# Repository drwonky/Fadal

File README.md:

# Fadal
Fadal reverse engineering schematics

- eagle/ contains some older Eagle schematics
- kicad/ contains imported Eagle schematics and some native schematics

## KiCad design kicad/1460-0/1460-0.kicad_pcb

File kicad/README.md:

## Fadal schematics
---
#### Note
The path to the S100.lbr was changed before committing to this repo to redact path names, you will need to update this yourself if you want to reference the S100 components.
---
- 1030-0e - imported from eagle
- 1090-2 - imported from eagle
- 1400-1A - imported from eagle
- 1420-1 - imported from eagle
- 1460-0 - Schematic and board layout, no routing
- components - custom componentes
- P8212.zip - Online EDA conversion of S100 component
- P8216.zip - Online EDA conversion of S100 component
- P8284.zip - Online EDA conversion of S100 component
- S100_MALE.kicad_mod - Kicad conversion
- S100_MALE.zip - Online EDA conversion of S100 component

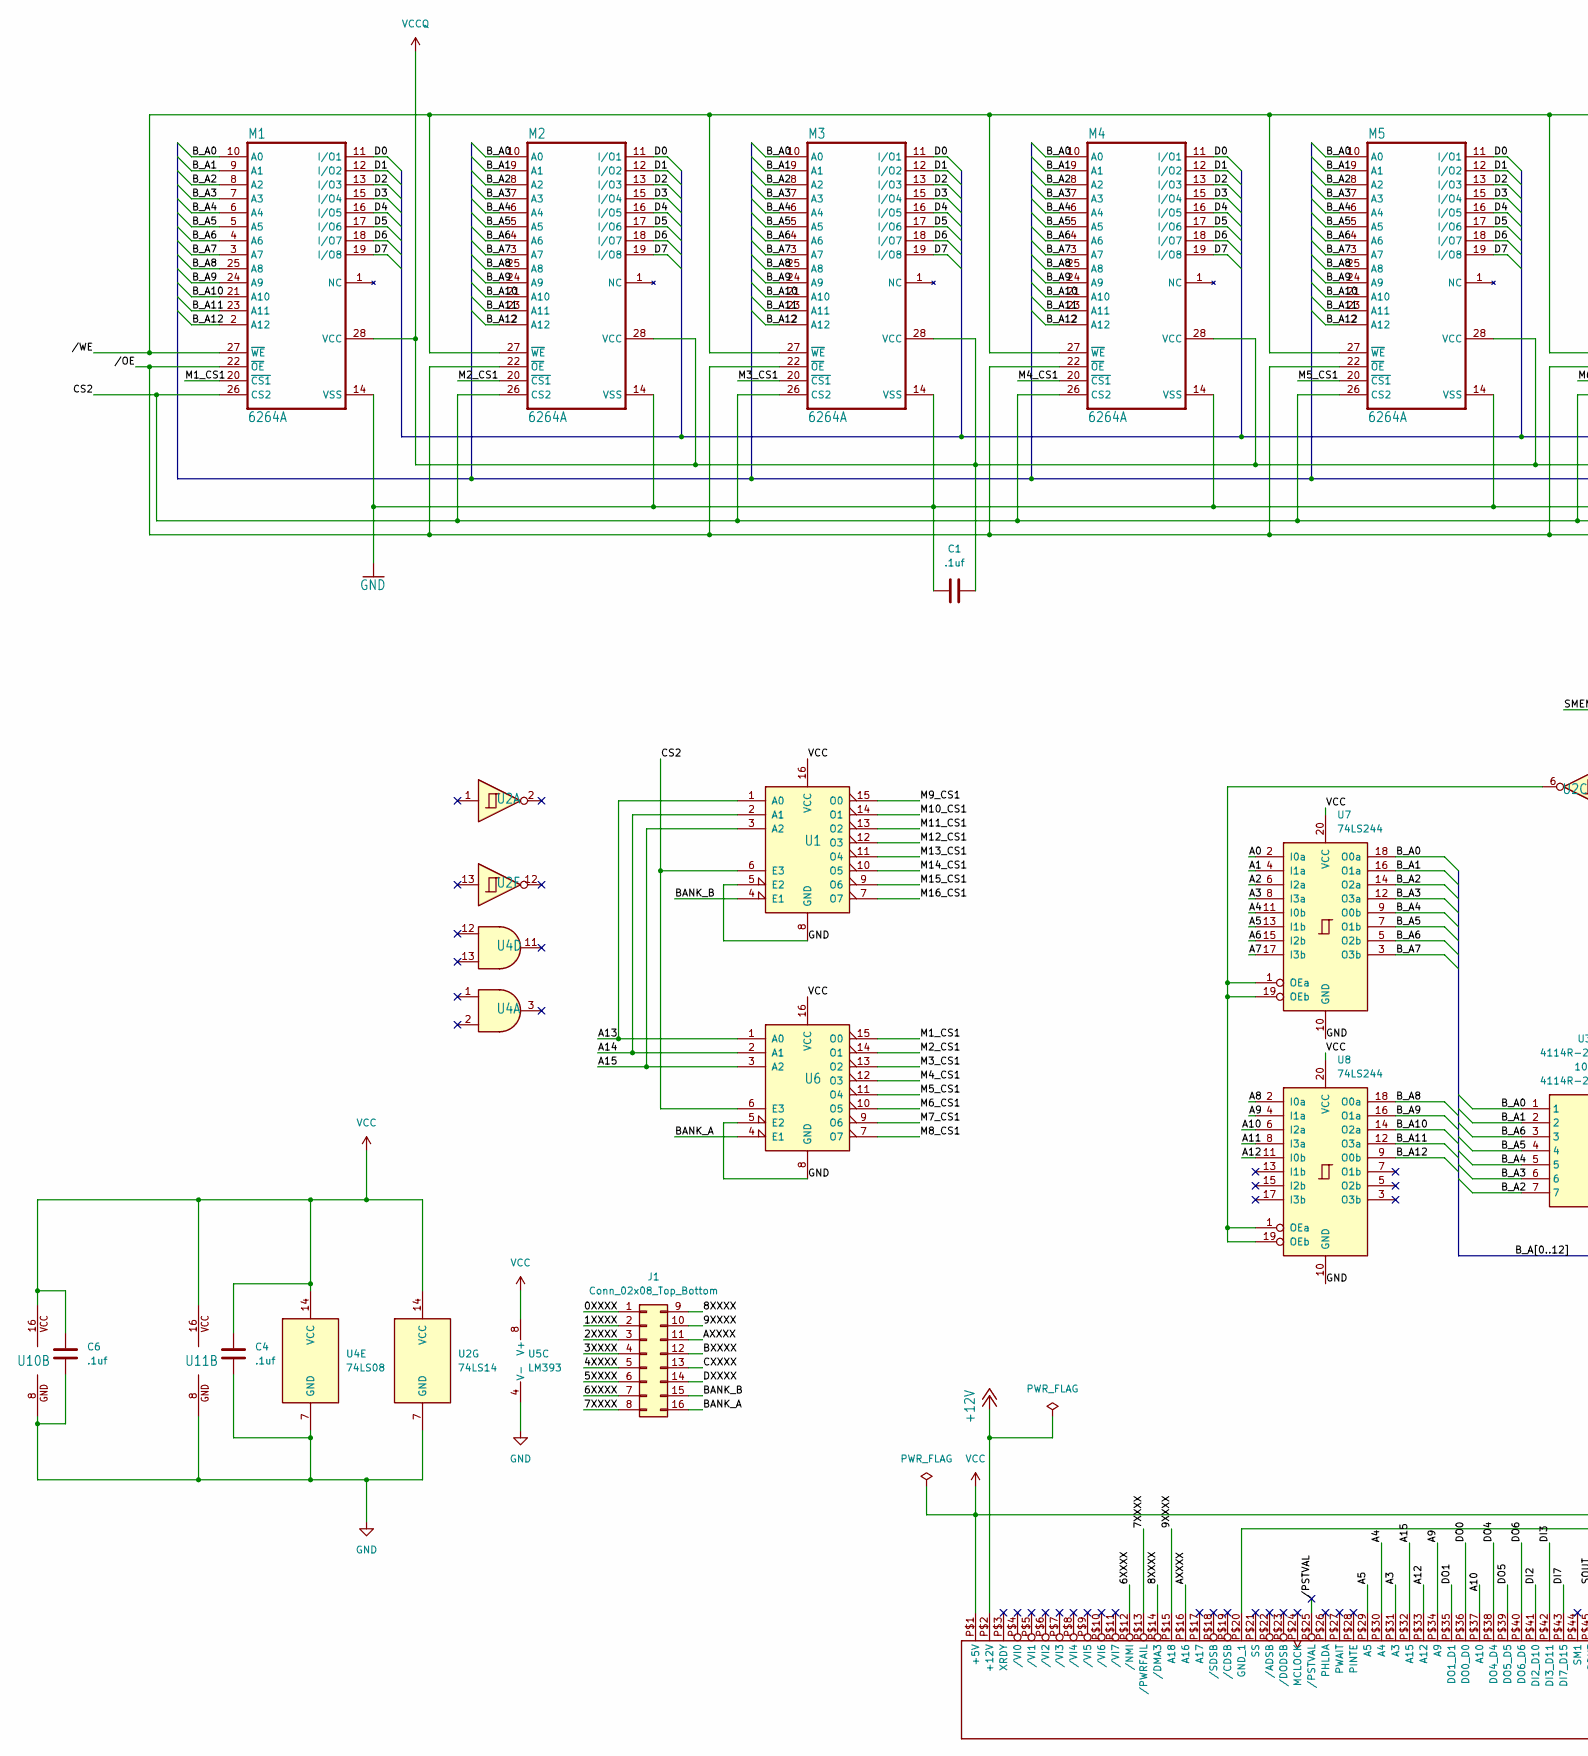
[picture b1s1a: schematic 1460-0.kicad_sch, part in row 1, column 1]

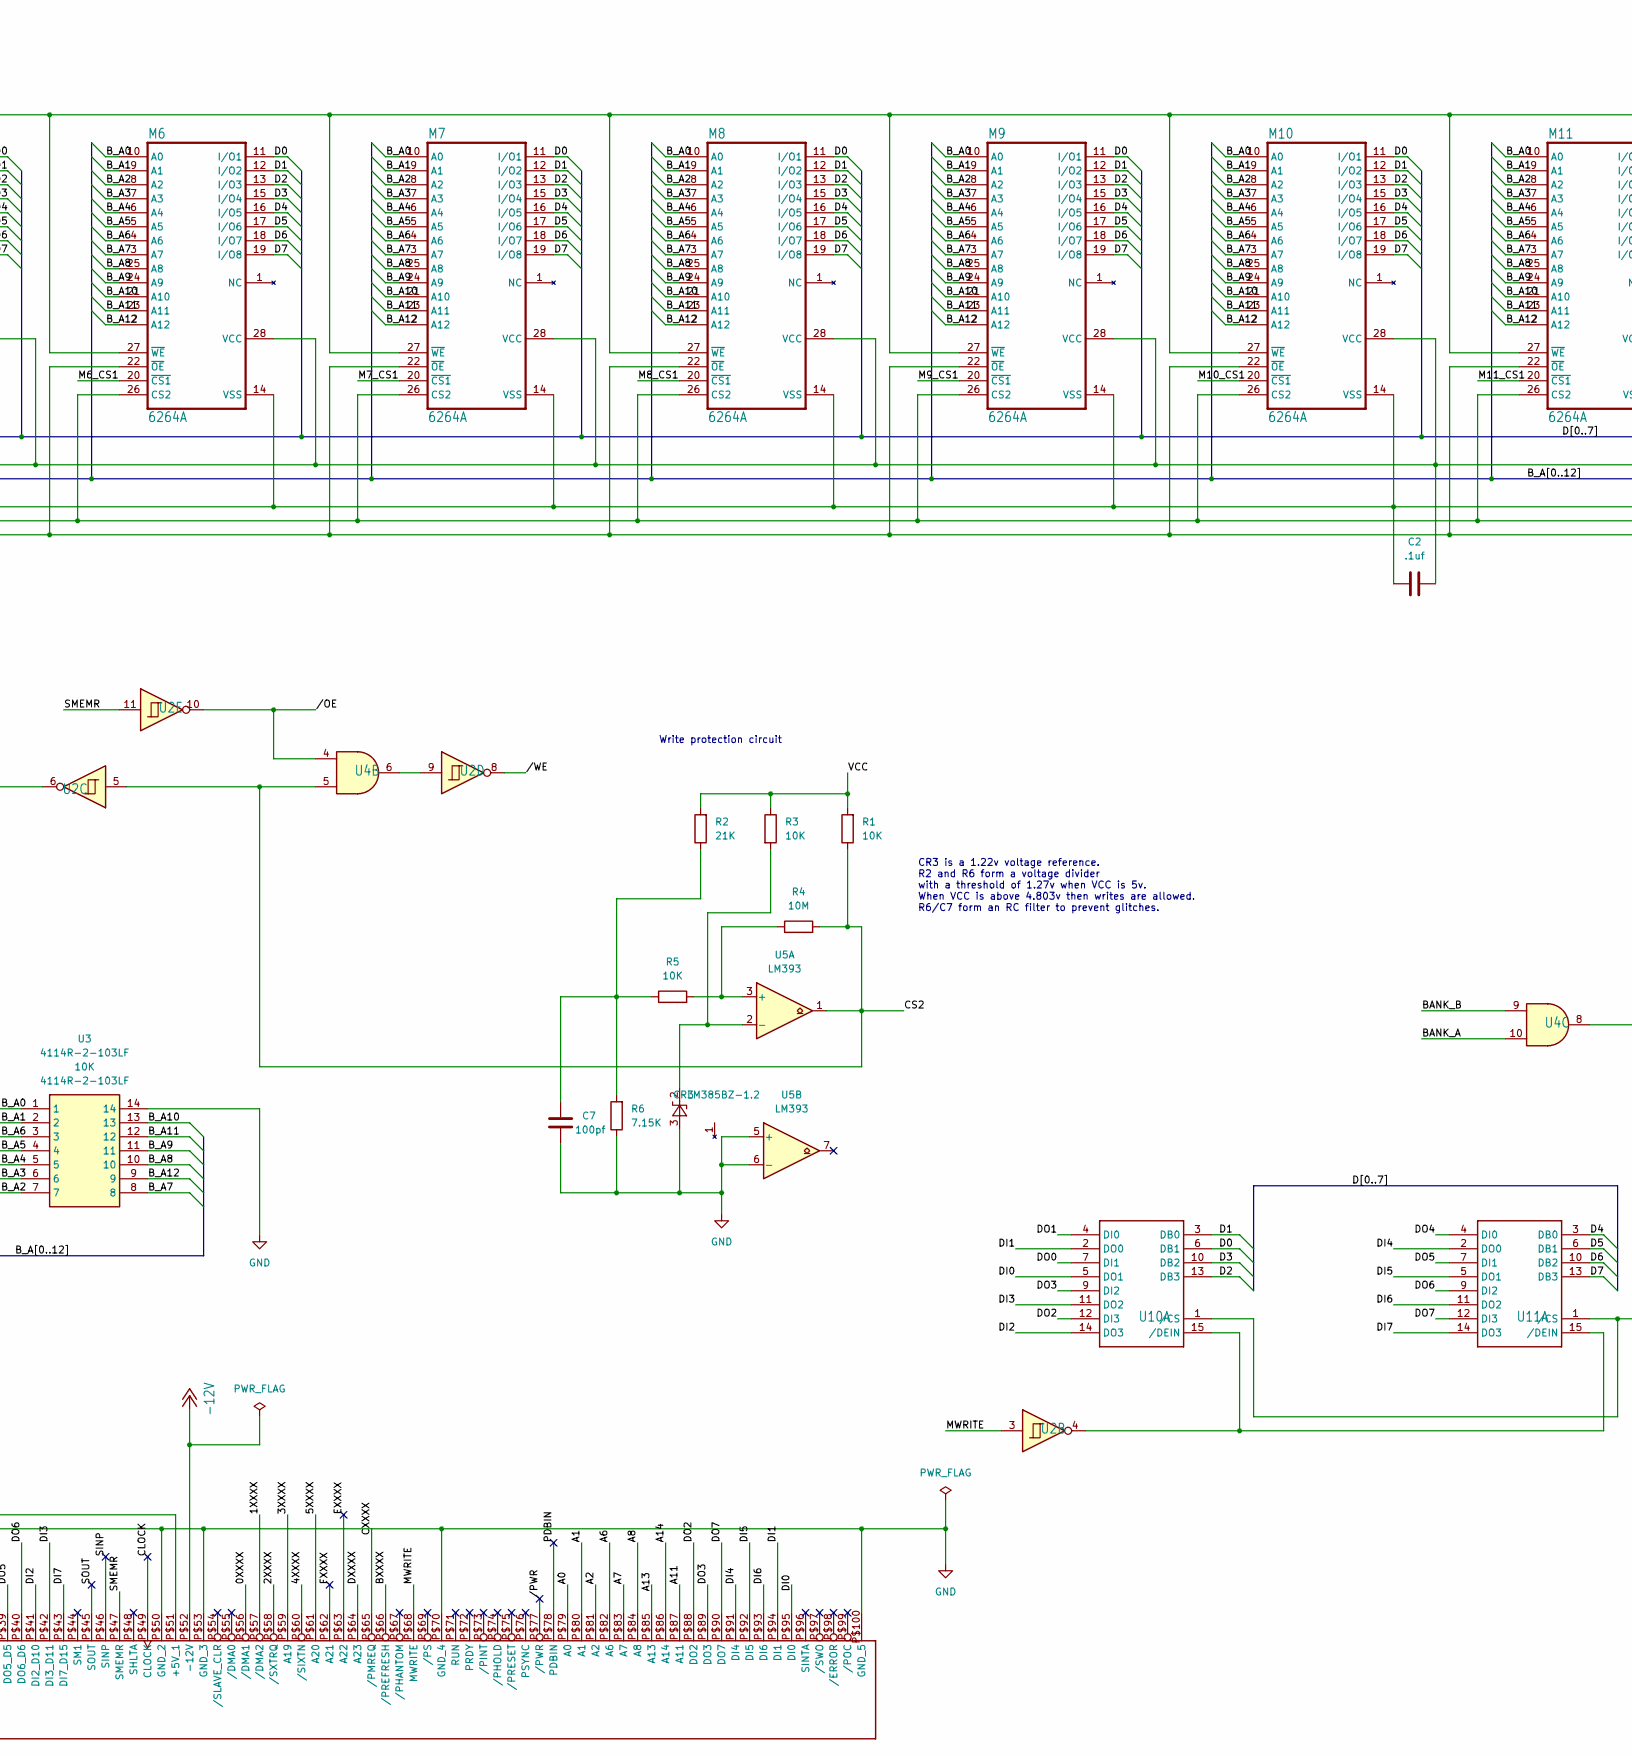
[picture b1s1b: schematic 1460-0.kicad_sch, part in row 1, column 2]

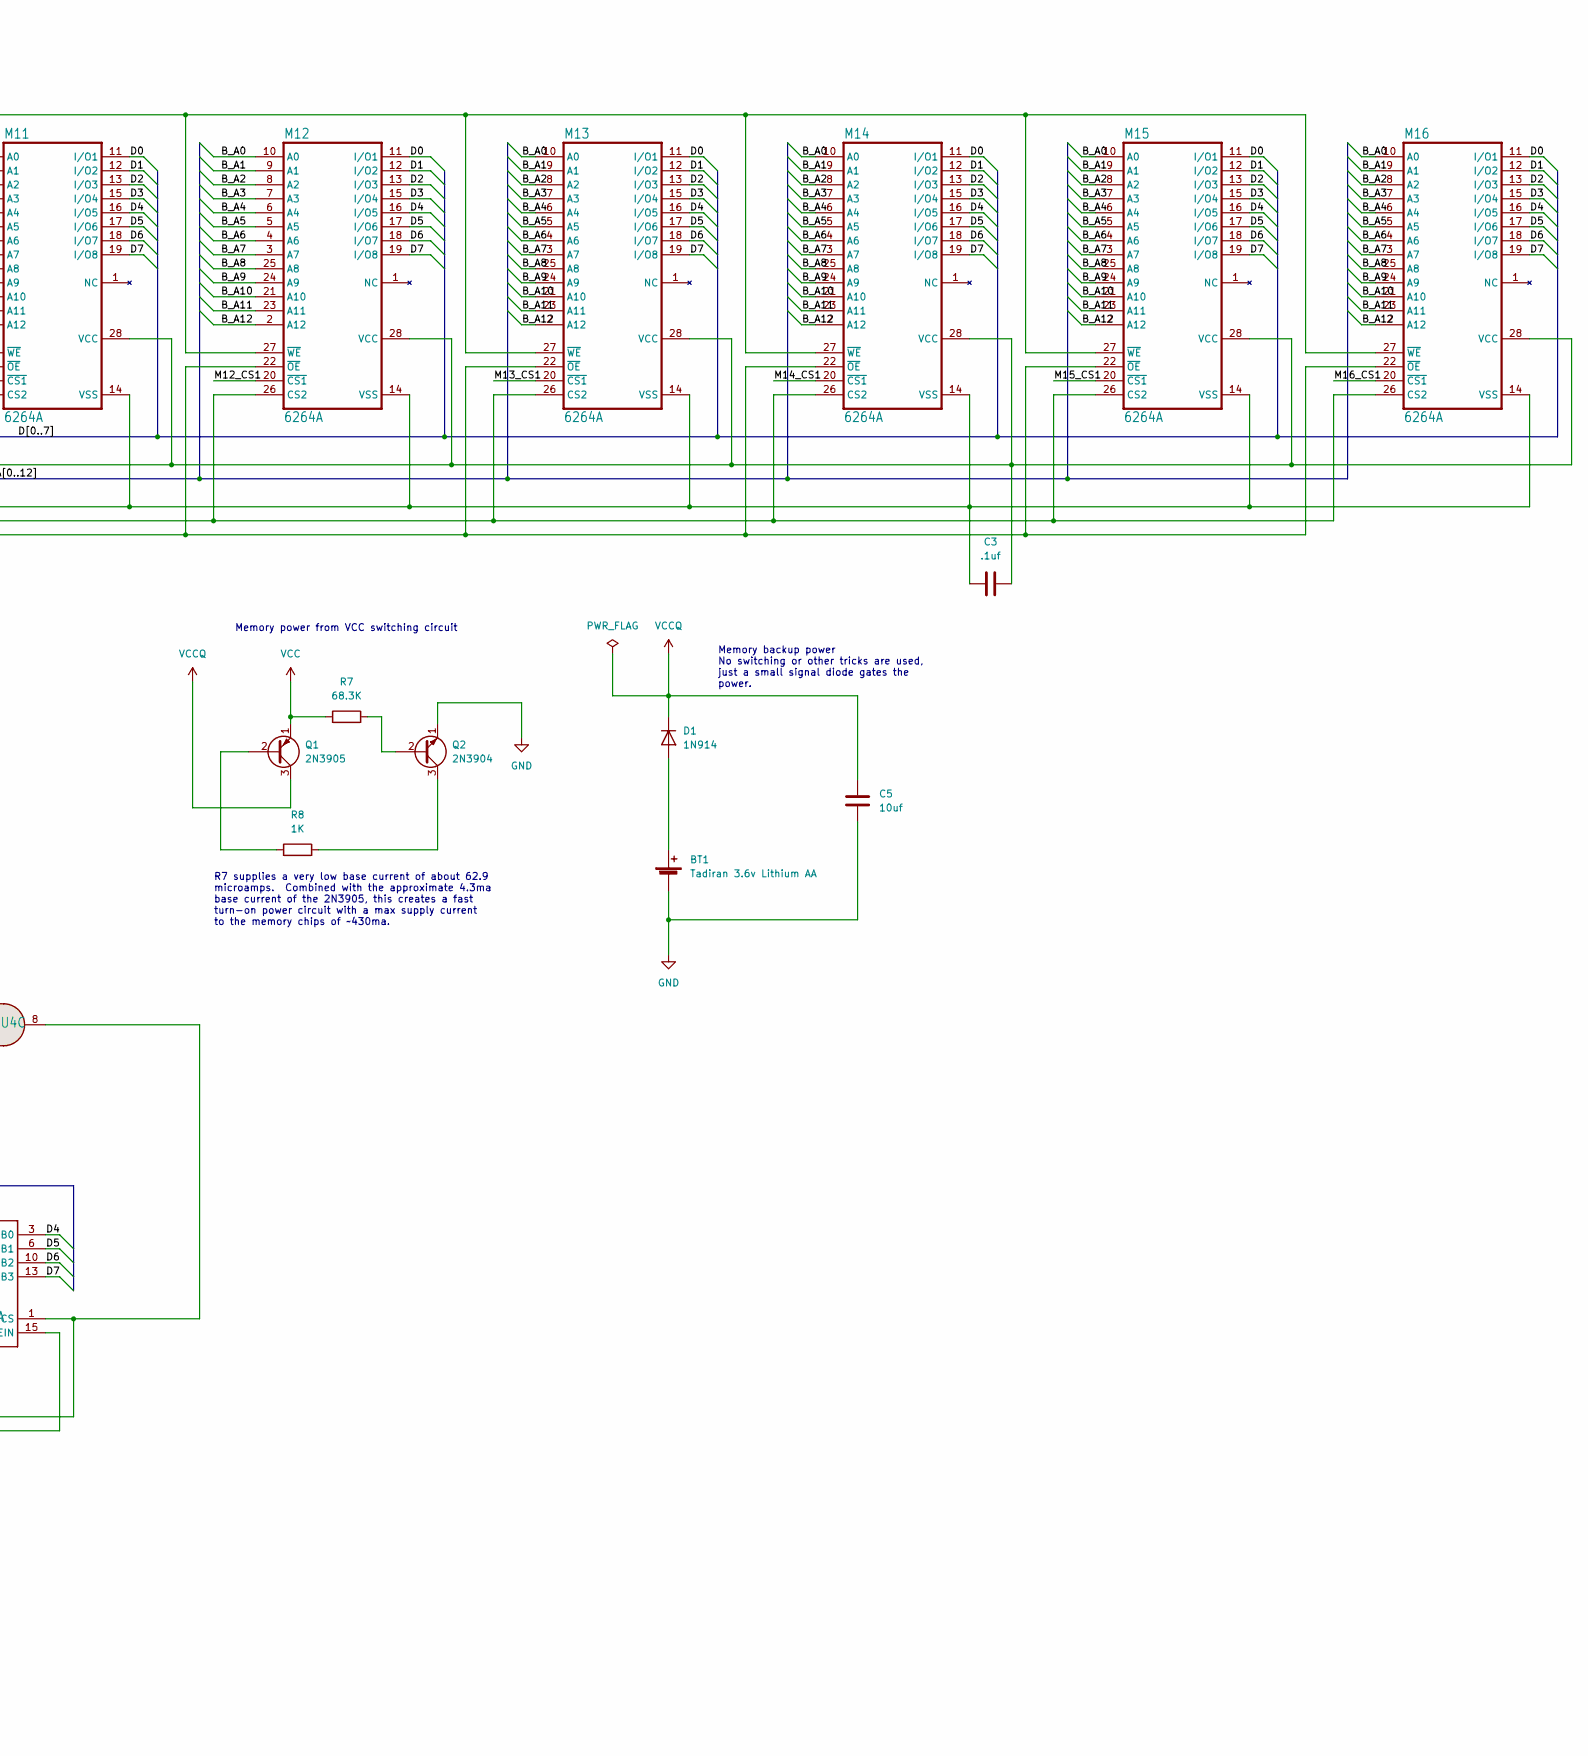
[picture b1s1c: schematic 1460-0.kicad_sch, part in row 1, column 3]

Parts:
BT1: Tadiran 3.6v Lithium AA; BatteryHolder_Keystone_2460_1xAA
C1, C2, C3, C4, C6: .1uf; C_Disc_D7.5mm_W5.0mm_P7.50mm
C5: 10uf; CP_Radial_Tantal_D7.0mm_P5.00mm
C7: 100pf; C_Disc_D7.5mm_W5.0mm_P7.50mm
CR3: LM385BZ-1.2; TO-92_Inline
D1: 1N914; D_DO-35_SOD27_P7.62mm_Horizontal
J1: Conn_02x08_Top_Bottom; DIP-16_W7.62mm_Socket_LongPads
M1, M2, M3, M4, M5, M6, M7, M8, M9, M10, M11, M12, M13, M14, M15, M16: 6264A; DIP-28_W15.24mm_LongPads
Q1: 2N3905; TO-92_Inline
Q2: 2N3904; TO-92_Inline
R1, R3, R5: 10K; R_Axial_DIN0309_L9.0mm_D3.2mm_P12.70mm_Horizontal
R2: 21K; R_Axial_DIN0309_L9.0mm_D3.2mm_P12.70mm_Horizontal
R4: 10M; R_Axial_DIN0309_L9.0mm_D3.2mm_P12.70mm_Horizontal
R6: 7.15K; R_Axial_DIN0309_L9.0mm_D3.2mm_P12.70mm_Horizontal
R7: 68.3K; R_Axial_DIN0309_L9.0mm_D3.2mm_P12.70mm_Horizontal
R8: 1K; R_Axial_DIN0309_L9.0mm_D3.2mm_P12.70mm_Horizontal
U1, U6: 74138N; DIP-16_W7.62mm_LongPads
U2: 74LS14; DIP-14_W7.62mm_LongPads
U3: 4114R-2-103LF; DIP-14_W7.62mm_LongPads; Manufacturer_Part_Number 4114R-2-103LF; Mouser Part Number 652-4114R-2LF-10K
U4: 74LS08; DIP-14_W7.62mm_LongPads
U5: LM393; DIP-8_W7.62mm_LongPads
U7, U8: 74LS244; DIP-20_W7.62mm_LongPads
U10, U11: P8216; DIP-16_W7.62mm_LongPads
U$1: S100_MALE

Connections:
+12V: U$1.P$2 (+12V)
-12V: U$1.P$52 (-12V)
/0XXXX: J1.1, U$1.P$56 (/DMA1)
/1XXXX: J1.2, U$1.P$57 (/DMA2)
/2XXXX: J1.3, U$1.P$58 (/SXTRQ)
/3XXXX: J1.4, U$1.P$59 (A19)
/4XXXX: J1.5, U$1.P$60 (/SIXTN)
/5XXXX: J1.6, U$1.P$61 (A20)
/6XXXX: J1.7, U$1.P$12 (/NMI)
/7XXXX: J1.8, U$1.P$13 (/PWRFAIL)
/8XXXX: J1.9, U$1.P$14 (/DMA3)
/9XXXX: J1.10, U$1.P$15 (A18)
/A0: U7.2 (I0a), U$1.P$79 (A0)
/A1: U7.4 (I1a), U$1.P$80 (A1)
/A2: U7.6 (I2a), U$1.P$81 (A2)
/A3: U7.8 (I3a), U$1.P$31 (A3)
/A4: U7.11 (I0b), U$1.P$30 (A4)
/A5: U7.13 (I1b), U$1.P$29 (A5)
/A6: U7.15 (I2b), U$1.P$82 (A6)
/A7: U7.17 (I3b), U$1.P$83 (A7)
/A8: U8.2 (I0a), U$1.P$84 (A8)
/A9: U8.4 (I1a), U$1.P$34 (A9)
/A10: U8.6 (I2a), U$1.P$37 (A10)
/A11: U8.8 (I3a), U$1.P$87 (A11)
/A12: U8.11 (I0b), U$1.P$33 (A12)
/A13: U1.1 (A0), U6.1 (A0), U$1.P$85 (A13)
/A14: U1.2 (A1), U6.2 (A1), U$1.P$86 (A14)
/A15: U1.3 (A2), U6.3 (A2), U$1.P$32 (A15)
/AXXXX: J1.11, U$1.P$16 (A16)
/BANK_A: J1.16, U4.10, U6.4 (E1)
/BANK_B: J1.15, U1.4 (E1), U4.9
/BXXXX: J1.12, U$1.P$66 (/PREFRESH)
/B_A0: M1.10 (A0), M2.10 (A0), M3.10 (A0), M4.10 (A0), M5.10 (A0), M6.10 (A0), M7.10 (A0), M8.10 (A0), M9.10 (A0), M10.10 (A0), M11.10 (A0), M12.10 (A0), M13.10 (A0), M14.10 (A0), M15.10 (A0), M16.10 (A0), U3.1, U7.18 (O0a)
/B_A1: M1.9 (A1), M2.9 (A1), M3.9 (A1), M4.9 (A1), M5.9 (A1), M6.9 (A1), M7.9 (A1), M8.9 (A1), M9.9 (A1), M10.9 (A1), M11.9 (A1), M12.9 (A1), M13.9 (A1), M14.9 (A1), M15.9 (A1), M16.9 (A1), U3.2, U7.16 (O1a)
/B_A2: M1.8 (A2), M2.8 (A2), M3.8 (A2), M4.8 (A2), M5.8 (A2), M6.8 (A2), M7.8 (A2), M8.8 (A2), M9.8 (A2), M10.8 (A2), M11.8 (A2), M12.8 (A2), M13.8 (A2), M14.8 (A2), M15.8 (A2), M16.8 (A2), U3.7, U7.14 (O2a)
/B_A3: M1.7 (A3), M2.7 (A3), M3.7 (A3), M4.7 (A3), M5.7 (A3), M6.7 (A3), M7.7 (A3), M8.7 (A3), M9.7 (A3), M10.7 (A3), M11.7 (A3), M12.7 (A3), M13.7 (A3), M14.7 (A3), M15.7 (A3), M16.7 (A3), U3.6, U7.12 (O3a)
/B_A4: M1.6 (A4), M2.6 (A4), M3.6 (A4), M4.6 (A4), M5.6 (A4), M6.6 (A4), M7.6 (A4), M8.6 (A4), M9.6 (A4), M10.6 (A4), M11.6 (A4), M12.6 (A4), M13.6 (A4), M14.6 (A4), M15.6 (A4), M16.6 (A4), U3.5, U7.9 (O0b)
/B_A5: M1.5 (A5), M2.5 (A5), M3.5 (A5), M4.5 (A5), M5.5 (A5), M6.5 (A5), M7.5 (A5), M8.5 (A5), M9.5 (A5), M10.5 (A5), M11.5 (A5), M12.5 (A5), M13.5 (A5), M14.5 (A5), M15.5 (A5), M16.5 (A5), U3.4, U7.7 (O1b)
/B_A6: M1.4 (A6), M2.4 (A6), M3.4 (A6), M4.4 (A6), M5.4 (A6), M6.4 (A6), M7.4 (A6), M8.4 (A6), M9.4 (A6), M10.4 (A6), M11.4 (A6), M12.4 (A6), M13.4 (A6), M14.4 (A6), M15.4 (A6), M16.4 (A6), U3.3, U7.5 (O2b)
/B_A7: M1.3 (A7), M2.3 (A7), M3.3 (A7), M4.3 (A7), M5.3 (A7), M6.3 (A7), M7.3 (A7), M8.3 (A7), M9.3 (A7), M10.3 (A7), M11.3 (A7), M12.3 (A7), M13.3 (A7), M14.3 (A7), M15.3 (A7), M16.3 (A7), U3.8, U7.3 (O3b)
/B_A8: M1.25 (A8), M2.25 (A8), M3.25 (A8), M4.25 (A8), M5.25 (A8), M6.25 (A8), M7.25 (A8), M8.25 (A8), M9.25 (A8), M10.25 (A8), M11.25 (A8), M12.25 (A8), M13.25 (A8), M14.25 (A8), M15.25 (A8), M16.25 (A8), U3.10, U8.18 (O0a)
/B_A9: M1.24 (A9), M2.24 (A9), M3.24 (A9), M4.24 (A9), M5.24 (A9), M6.24 (A9), M7.24 (A9), M8.24 (A9), M9.24 (A9), M10.24 (A9), M11.24 (A9), M12.24 (A9), M13.24 (A9), M14.24 (A9), M15.24 (A9), M16.24 (A9), U3.11, U8.16 (O1a)
/B_A10: M1.21 (A10), M2.21 (A10), M3.21 (A10), M4.21 (A10), M5.21 (A10), M6.21 (A10), M7.21 (A10), M8.21 (A10), M9.21 (A10), M10.21 (A10), M11.21 (A10), M12.21 (A10), M13.21 (A10), M14.21 (A10), M15.21 (A10), M16.21 (A10), U3.13, U8.14 (O2a)
/B_A11: M1.23 (A11), M2.23 (A11), M3.23 (A11), M4.23 (A11), M5.23 (A11), M6.23 (A11), M7.23 (A11), M8.23 (A11), M9.23 (A11), M10.23 (A11), M11.23 (A11), M12.23 (A11), M13.23 (A11), M14.23 (A11), M15.23 (A11), M16.23 (A11), U3.12, U8.12 (O3a)
/B_A12: M1.2 (A12), M2.2 (A12), M3.2 (A12), M4.2 (A12), M5.2 (A12), M6.2 (A12), M7.2 (A12), M8.2 (A12), M9.2 (A12), M10.2 (A12), M11.2 (A12), M12.2 (A12), M13.2 (A12), M14.2 (A12), M15.2 (A12), M16.2 (A12), U3.9, U8.9 (O0b)
/CLOCK: U$1.P$49 (CLOCK)
/CS2: M1.26 (CS2), M2.26 (CS2), M3.26 (CS2), M4.26 (CS2), M5.26 (CS2), M6.26 (CS2), M7.26 (CS2), M8.26 (CS2), M9.26 (CS2), M10.26 (CS2), M11.26 (CS2), M12.26 (CS2), M13.26 (CS2), M14.26 (CS2), M15.26 (CS2), M16.26 (CS2), R1.1, R4.2, U1.6 (E3), U2.5, U4.5, U5.1, U6.6 (E3)
/CXXXX: J1.13, U$1.P$65 (/PMREQ)
/D0: M1.11 (I/O1), M2.11 (I/O1), M3.11 (I/O1), M4.11 (I/O1), M5.11 (I/O1), M6.11 (I/O1), M7.11 (I/O1), M8.11 (I/O1), M9.11 (I/O1), M10.11 (I/O1), M11.11 (I/O1), M12.11 (I/O1), M13.11 (I/O1), M14.11 (I/O1), M15.11 (I/O1), M16.11 (I/O1), U10.6 (DB1)
/D1: M1.12 (I/O2), M2.12 (I/O2), M3.12 (I/O2), M4.12 (I/O2), M5.12 (I/O2), M6.12 (I/O2), M7.12 (I/O2), M8.12 (I/O2), M9.12 (I/O2), M10.12 (I/O2), M11.12 (I/O2), M12.12 (I/O2), M13.12 (I/O2), M14.12 (I/O2), M15.12 (I/O2), M16.12 (I/O2), U10.3 (DB0)
/D2: M1.13 (I/O3), M2.13 (I/O3), M3.13 (I/O3), M4.13 (I/O3), M5.13 (I/O3), M6.13 (I/O3), M7.13 (I/O3), M8.13 (I/O3), M9.13 (I/O3), M10.13 (I/O3), M11.13 (I/O3), M12.13 (I/O3), M13.13 (I/O3), M14.13 (I/O3), M15.13 (I/O3), M16.13 (I/O3), U10.13 (DB3)
/D3: M1.15 (I/O4), M2.15 (I/O4), M3.15 (I/O4), M4.15 (I/O4), M5.15 (I/O4), M6.15 (I/O4), M7.15 (I/O4), M8.15 (I/O4), M9.15 (I/O4), M10.15 (I/O4), M11.15 (I/O4), M12.15 (I/O4), M13.15 (I/O4), M14.15 (I/O4), M15.15 (I/O4), M16.15 (I/O4), U10.10 (DB2)
/D4: M1.16 (I/O5), M2.16 (I/O5), M3.16 (I/O5), M4.16 (I/O5), M5.16 (I/O5), M6.16 (I/O5), M7.16 (I/O5), M8.16 (I/O5), M9.16 (I/O5), M10.16 (I/O5), M11.16 (I/O5), M12.16 (I/O5), M13.16 (I/O5), M14.16 (I/O5), M15.16 (I/O5), M16.16 (I/O5), U11.3 (DB0)
/D5: M1.17 (I/O6), M2.17 (I/O6), M3.17 (I/O6), M4.17 (I/O6), M5.17 (I/O6), M6.17 (I/O6), M7.17 (I/O6), M8.17 (I/O6), M9.17 (I/O6), M10.17 (I/O6), M11.17 (I/O6), M12.17 (I/O6), M13.17 (I/O6), M14.17 (I/O6), M15.17 (I/O6), M16.17 (I/O6), U11.6 (DB1)
/D6: M1.18 (I/O7), M2.18 (I/O7), M3.18 (I/O7), M4.18 (I/O7), M5.18 (I/O7), M6.18 (I/O7), M7.18 (I/O7), M8.18 (I/O7), M9.18 (I/O7), M10.18 (I/O7), M11.18 (I/O7), M12.18 (I/O7), M13.18 (I/O7), M14.18 (I/O7), M15.18 (I/O7), M16.18 (I/O7), U11.10 (DB2)
/D7: M1.19 (I/O8), M2.19 (I/O8), M3.19 (I/O8), M4.19 (I/O8), M5.19 (I/O8), M6.19 (I/O8), M7.19 (I/O8), M8.19 (I/O8), M9.19 (I/O8), M10.19 (I/O8), M11.19 (I/O8), M12.19 (I/O8), M13.19 (I/O8), M14.19 (I/O8), M15.19 (I/O8), M16.19 (I/O8), U11.13 (DB3)
/DI0: U10.5 (DO1), U$1.P$95 (DI0)
/DI1: U10.2 (DO0), U$1.P$94 (DI1)
/DI2: U10.14 (DO3), U$1.P$41 (DI2_D10)
/DI3: U10.11 (DO2), U$1.P$42 (DI3_D11)
/DI4: U11.2 (DO0), U$1.P$91 (DI4)
/DI5: U11.5 (DO1), U$1.P$92 (DI5)
/DI6: U11.11 (DO2), U$1.P$93 (DI6)
/DI7: U11.14 (DO3), U$1.P$43 (DI7_D15)
/DO0: U10.7 (DI1), U$1.P$36 (DO0_D0)
/DO1: U10.4 (DI0), U$1.P$35 (DO1_D1)
/DO2: U10.12 (DI3), U$1.P$88 (DO2)
/DO3: U10.9 (DI2), U$1.P$89 (DO3)
/DO4: U11.4 (DI0), U$1.P$38 (DO4_D4)
/DO5: U11.7 (DI1), U$1.P$39 (DO5_D5)
/DO6: U11.9 (DI2), U$1.P$40 (DO6_D6)
/DO7: U11.12 (DI3), U$1.P$90 (DO7)
/DXXXX: J1.14, U$1.P$64 (A23)
/EXXXX: U$1.P$63 (A22)
/FXXXX: U$1.P$62 (A21)
/M1_CS1: M1.20 (~CS1), U6.15 (O0)
/M2_CS1: M2.20 (~CS1), U6.14 (O1)
/M3_CS1: M3.20 (~CS1), U6.13 (O2)
/M4_CS1: M4.20 (~CS1), U6.12 (O3)
/M5_CS1: M5.20 (~CS1), U6.11 (O4)
/M6_CS1: M6.20 (~CS1), U6.10 (O5)
/M7_CS1: M7.20 (~CS1), U6.9 (O6)
/M8_CS1: M8.20 (~CS1), U6.7 (O7)
/M9_CS1: M9.20 (~CS1), U1.15 (O0)
/M10_CS1: M10.20 (~CS1), U1.14 (O1)
/M11_CS1: M11.20 (~CS1), U1.13 (O2)
/M12_CS1: M12.20 (~CS1), U1.12 (O3)
/M13_CS1: M13.20 (~CS1), U1.11 (O4)
/M14_CS1: M14.20 (~CS1), U1.10 (O5)
/M15_CS1: M15.20 (~CS1), U1.9 (O6)
/M16_CS1: M16.20 (~CS1), U1.7 (O7)
/MWRITE: U2.3, U$1.P$68 (MWRITE)
/PDBIN: U$1.P$78 (PDBIN)
/SINP: U$1.P$46 (SINP)
/SMEMR: U2.11, U$1.P$47 (SMEMR)
/SOUT: U$1.P$45 (SOUT)
//PSTVAL: U$1.P$25 (/PSTVAL)
//PWR: U$1.P$77 (/PWR)
GND: BT1.2 (-), C1.2, C2.2, C3.2, C4.2, C5.2, C6.2, C7.2, CR3.3 (A), M1.14 (VSS), M2.14 (VSS), M3.14 (VSS), M4.14 (VSS), M5.14 (VSS), M6.14 (VSS), M7.14 (VSS), M8.14 (VSS), M9.14 (VSS), M10.14 (VSS), M11.14 (VSS), M12.14 (VSS), M13.14 (VSS), M14.14 (VSS), M15.14 (VSS), M16.14 (VSS), Q2.1 (E), R6.1, U1.5 (E2), U1.8 (GND), U2.7 (GND), U3.14, U4.7 (GND), U5.4 (V-), U5.5 (+), U5.6 (-), U6.5 (E2), U6.8 (GND), U7.10 (GND), U8.10 (GND), U10.8 (GND), U11.8 (GND), U$1.P$20 (GND_1), U$1.P$50 (GND_2), U$1.P$53 (GND_3), U$1.P$70 (GND_4), U$1.P$100 (GND_5)
unnamed: BT1.1 (+), D1.2 (A)
unnamed: CR3.2 (K), R3.2, U5.2 (-)
unnamed: Q2.2 (B), R7.2
unnamed: Q2.3 (C), R8.2
unnamed: C7.1, R2.1, R5.1, R6.2
unnamed: R4.1, R5.2, U5.3 (+)
unnamed: Q1.2 (B), R8.1
unnamed: U2.9, U4.6
unnamed: U2.6, U7.1 (OEa), U7.19 (OEb), U8.1 (OEa), U8.19 (OEb)
unnamed: U4.8, U10.1 (/CS), U11.1 (/CS)
unnamed: U2.4, U10.15 (/DEIN), U11.15 (/DEIN)
VCC: C4.1, C6.1, Q1.1 (E), R1.2, R2.2, R3.1, R7.1, U1.16 (VCC), U2.14 (VCC), U4.14 (VCC), U5.8 (V+), U6.16 (VCC), U7.20 (VCC), U8.20 (VCC), U10.16 (VCC), U11.16 (VCC), U$1.P$1 (+5V), U$1.P$51 (+5V_1)
VCCQ: C1.1, C2.1, C3.1, C5.1, D1.1 (K), M1.28 (VCC), M2.28 (VCC), M3.28 (VCC), M4.28 (VCC), M5.28 (VCC), M6.28 (VCC), M7.28 (VCC), M8.28 (VCC), M9.28 (VCC), M10.28 (VCC), M11.28 (VCC), M12.28 (VCC), M13.28 (VCC), M14.28 (VCC), M15.28 (VCC), M16.28 (VCC), Q1.3 (C)

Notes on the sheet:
Memory backup power No switching or other tricks are used, just a small signal diode gates the power.
Memory power from VCC switching circuit
CR3 is a 1.22v voltage reference. R2 and R6 form a voltage divider with a threshold of 1.27v when VCC is 5v. When VCC is above 4.803v then writes are allowed. R6/C7 form an RC filter to prevent glitches.
R7 supplies a very low base current of about 62.9 microamps. Combined with the approximate 4.3ma base current of the 2N3905, this creates a fast turn-on power circuit with a max supply current to the memory chips of ~430ma.
Write protection circuit

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
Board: 2 copper layers, 48 parts (0 on the bottom side), 104 nets, no tracks yet.

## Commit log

2023-05-16 Added READMEs
2023-05-16 Fixing README formatting
2023-05-27 Updated 1460-0 schematic to match board exactly
    Made changes to the edge connector symbol to remove unconnected pads
